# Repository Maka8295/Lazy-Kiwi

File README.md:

# Lazy-Kiwi
ESP32 based smart home device

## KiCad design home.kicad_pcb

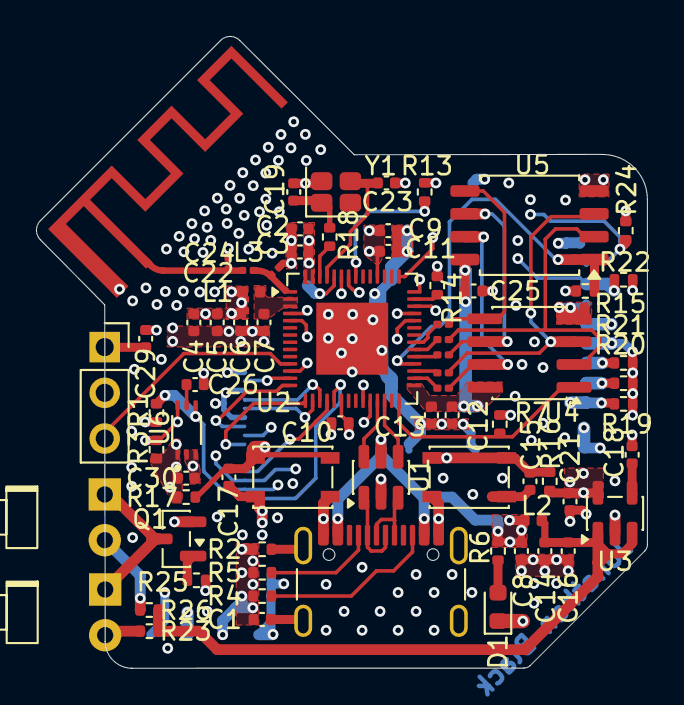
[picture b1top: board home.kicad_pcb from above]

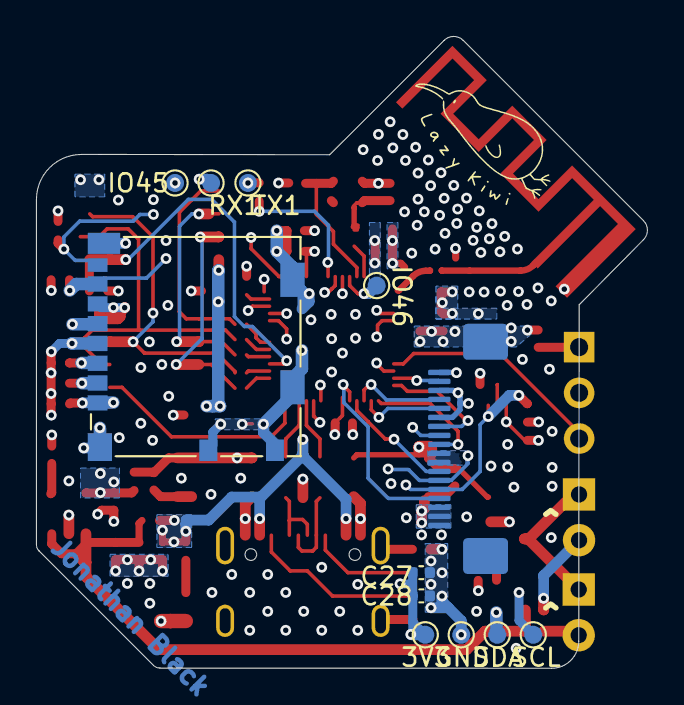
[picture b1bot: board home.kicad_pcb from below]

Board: 6 copper layers, 33.9 x 35.1 mm, 84 parts (12 on the bottom side), 60 nets.

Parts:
3V3: TestPoint; TestPoint_Pad_D1.0mm
ANT1: 50Ohm 2.4GHz PCB ANT; 2.4GHz Antenna
C1: 2.2nF; C_0402_1005Metric
C2, C5, C9, C13, C26, C27: 1uF; C_0402_1005Metric
C3: 10nF; C_0402_1005Metric
C4, C16, C21: 10uF; C_0402_1005Metric
C6, C7, C8, C10, C11, C12, C14, C15, C17, C18, C25, C28, C29, C30: 100nF; C_0402_1005Metric
C19, C23: 20pF; C_0402_1005Metric
C22, C24: 3p3F; C_0201_0603Metric
D1: LED; LED_0603_1608Metric
D3: 940nm; LED_D1.8mm_W1.8mm_H2.4mm_Horizontal_O3.81mm_Z1.6mm
GND: TestPoint; TestPoint_Pad_D1.0mm
IO45, IO46: TestPoint; TestPoint_Pad_D1.0mm
J1: USB_C_Receptacle_USB2.0_14P; USB_C_Receptacle_GCT_USB4105-xx-A_16P_TopMnt_Horizontal
J3: DISPLAY; LCSC FPC 18
J4: Micro_SD_Card; microSD_HC_Molex_104031-0811
J5: VS1838B IR Receiver; PinSocket_1x03_P2.54mm_Vertical
K^: 940nm; LED_D1.8mm_W1.8mm_H2.4mm_Horizontal_O3.81mm_Z1.6mm
L1, L2: 2n2H; L_0402_1005Metric
L3: 2n2H; L_0201_0603Metric
Q1: SS8050; SOT-23
R1, R3: 4.7kR; R_0402_1005Metric
R2: 1M; R_0402_1005Metric
R4, R5: 5.1k; R_0402_1005Metric
R6: 2.2k; R_0402_1005Metric
R7, R15, R16, R17, R19, R20, R21, R22, R24: 10k; R_0402_1005Metric
R8, R9, R10, R11, R12: 0R; R_0201_0603Metric
R13: 470R; R_0402_1005Metric
R14: 47R; R_0402_1005Metric
R18: 22R; R_0402_1005Metric
R23, R26: 47; R_0402_1005Metric
R25: 1k; R_0402_1005Metric
RX1: TestPoint; TestPoint_Pad_D1.0mm
SCL: TestPoint; TestPoint_Pad_D1.0mm
SDA: TestPoint; TestPoint_Pad_D1.0mm
SW1, SW2: SW_Push; SW_SPST_PTS810
TX1: TestPoint; TestPoint_Pad_D1.0mm
U1: USBLC6-2SC6; SOT-23-6
U2: ESP32-S3; QFN-56-1EP_7x7mm_P0.4mm_EP4x4mm
U3: SPX3819M5-L-3-3; SOT-23-5
U4: ESP-PSRAM64H; SOIC-8_3.9x4.9mm_P1.27mm
U5: W25Q128JVSIQ; SOIC-8_5.3x5.3mm_P1.27mm
U6: BH1750FVI-TR; XDCR_BH1750FVI-TR
Y1: 40MHz; Crystal_SMD_EuroQuartz_X22-4Pin_2.5x2.0mm

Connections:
3V3: 3V3.1 (1_1), C2.1, C3.1, C4.2, C5.2, C6.2, C9.2, C10.2, C11.2, C21.2, C27.2, C28.2, C29.2, C30.2, J3.1, J4.4 (VDD), J5.1, L1.2, R1.2, R3.2, R7.2, R15.2, R16.2, R17.2, R19.2, R20.2, R21.2, R22.2, R24.2, U2.20 (VDD3P3_RTC), U2.46 (VDD3P3_CPU), U2.55 (VDDA), U2.56 (VDDA), U3.5 (OUT), U6.1 (VCC)
BOOT: C17.1, R17.1, SW2.2, U2.5 (GPIO0)
CLK: J4.5 (CLK), R14.1
CMD: J4.3 (CMD), R21.1, U2.40 (GPIO35)
D+: J1.A6 (D+), J1.B6 (D+), U1.3 (I/O2), U1.4 (I/O2), U2.26 (GPIO20/USB_D+)
D-: J1.A7 (D-), J1.B7 (D-), U1.1 (I/O1), U1.6 (I/O1), U2.25 (GPIO19/USB_D-)
DAT0: J4.7 (DAT0), R22.1, U2.42 (GPIO37)
DAT1: J4.8 (DAT1), R24.1, U2.43 (GPIO38)
DAT2: J4.1 (DAT2), R19.1, U2.38 (GPIO33)
DAT3: J4.2 (DAT3/CD), R20.1, U2.39 (GPIO34)
EN: C15.1, J3.8, R16.1, SW1.2, U2.4 (CHIP_PU)
FSPICLK: J3.4, U2.17 (GPIO12)
FSPICS0: J3.9, U2.15 (GPIO10)
FSPID: J3.5, U2.16 (GPIO11)
GND: ANT1.2 (GND), C1.1, C2.2, C3.2, C4.1, C5.1, C6.1, C7.1, C8.1, C9.1, C10.1, C11.1, C12.1, C13.1, C14.1, C15.2, C16.1, C17.2, C18.1, C19.2, C21.1, C22.1, C23.1, C24.1, C25.1, C26.1, C27.1, C28.1, C29.1, C30.1, D1.1 (K), GND.1 (1_1), J1.A1 (GND), J1.A12 (GND), J1.B1 (GND), J1.B12 (GND), J3.3, J3.6, J3.10, J3.11, J3.16, J3.17, J3.18, J3.GND, J4.6 (VSS), J4.9, J4.10, J4.SH (SHIELD), J5.2, Q1.2 (E), R2.1, R4.1, R5.1, SW1.1, SW2.1, U1.2 (GND), U2.57 (GND), U3.2 (GND), U4.4 (VSS), U5.4 (GND), U6.2 (ADDR), U6.3 (GND), Y1.2 (G), Y1.4 (G)
IO45: IO45.1 (1_1), U2.51 (GPIO45)
IO46: IO46.1 (1_1), U2.52 (GPIO46)
IR-IN: J5.3, U2.11 (GPIO6)
IR-OUT: R25.1, U2.12 (GPIO7)
LCD_BL: J3.2, U2.13 (GPIO8)
LCD_DC: J3.7, U2.14 (GPIO9)
LNA_IN: C22.2, L3.1, U2.1 (LNA_IN)
unnamed: ANT1.1 (LNA), C24.2, L3.2
unnamed: C7.2, L1.1, U2.2 (VDD3P3), U2.3 (VDD3P3)
unnamed: C19.1, R18.1, Y1.1
unnamed: D1.2 (A), R6.2
unnamed: K^.2 (A), R23.2
unnamed: D3.1 (K), K^.1 (K), Q1.3 (C)
unnamed: D3.2 (A), R26.1
unnamed: J1.A5 (CC1), R5.2
unnamed: J1.B5 (CC2), R4.2
unnamed: C1.2, J1.SH (SHIELD), R2.2
unnamed: Q1.1 (B), R25.2
unnamed: C8.2, J1.A4 (VBUS), J1.A9 (VBUS), J1.B4 (VBUS), J1.B9 (VBUS), L2.1, R6.1, U1.5 (VBUS)
unnamed: R14.2, U2.41 (GPIO36)
unnamed: R10.2, U2.33 (SPICLK)
unnamed: R12.2, U2.35 (SPID)
unnamed: R8.2, U2.30 (SPIHD)
unnamed: R11.2, U2.34 (SPIQ)
unnamed: R9.2, U2.31 (SPIWP)
unnamed: R13.2, U2.49 (U0TXD)
unnamed: C18.2, U3.4 (BP)
unnamed: C26.2, U6.5 (DVI)
RX: RX1.1 (1_1), U2.50 (U0RXD)
SCL: J3.13, R3.1, SCL.1 (1_1), U2.24 (GPIO18), U6.6 (SCL)
SDA: J3.14, R1.1, SDA.1 (1_1), U2.23 (GPIO17), U6.4 (SDA)
SPICLK: R10.1, U4.6 (SCLK), U5.6 (CLK)
SPICS0: R15.1, U2.32 (SPICS0), U5.1 (~CS)
SPICS1: R7.1, U2.28 (SPICS1), U4.1 (~CE)
SPID: R12.1, U4.5 (SI/SIO), U5.5 (DI/IO_{0})
SPIHD: R8.1, U4.7 (SIO3), U5.7 (~HOLD/~RESET/IO_{3})
SPIQ: R11.1, U4.2 (SO/SIO), U5.2 (DO/IO_{1})
SPIWP: R9.1, U4.3 (SIO2), U5.3 (~WP/IO_{2})
TP_INT: J3.15, U2.19 (GPIO14)
TP_RST: J3.12, U2.18 (GPIO13)
TX: R13.1, TX1.1 (1_1)
VBUS: C14.2, C16.2, L2.2, R23.1, R26.2, U3.1 (IN), U3.3 (EN)
VCC_SPI: C12.2, C13.2, C25.2, U2.29 (VDD_SPI), U4.8 (VCC), U5.8 (VCC)
XTAL_N: C23.2, U2.53 (XTAL_N), Y1.3
XTAL_P: R18.2, U2.54 (XTAL_P)

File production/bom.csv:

Designator,Footprint,Quantity,Value,LCSC Part #
ANT1,2.4GHz Antenna,1,50Ohm 2.4GHz PCB ANT,
"C1, L1, L2",0402,3,2n2,
"C10, C11, C12, C14, C15, C17, C18, C25, C26, C30, C31, C6, C7, C8",0402,14,100n,
"C13, C2, C27, C5, C9",0402,5,1u,
"C16, C21, C4",0402,3,10u,
"C19, C23",0402,2,20p,
"C22, C24",0201,2,3p3,
C28,0402,1,1uF,
C29,0402,1,100nF,
C3,0402,1,10n,
D1,0603,1,LED,
"D2, D3",LED_D1.8mm_W1.8mm_H2.4mm_Horizontal_O3.81mm_Z1.6mm,2,940nm,
J1,USB_C_Receptacle_GCT_USB4105-xx-A_16P_TopMnt_Horizontal,1,USB_C_Receptacle_USB2.0_14P,
J2,LCSC FPC 18,1,DISPLAY,
J3,microSD_HC_Molex_104031-0811,1,Micro_SD_Card,
J4,PinSocket_1x03_P2.54mm_Vertical,1,VS1838B IR Receiver,
L3,0201,1,2n2,
Q1,SOT-23,1,SS8050,
"R1, R3, R4, R5",0402,4,5k1,
"R10, R11, R12, R8, R9",0201,5,0R,
R13,0402,1,470,
R14,0402,1,47,
"R15, R16, R17, R19, R20, R21, R22, R24, R7",0402,9,10k,
R18,0402,1,22,
R2,0402,1,1M,
"R23, R26",0805,2,47,
R25,0402,1,1k,
R6,0402,1,2k1,
"SW1, SW2",SW_SPST_PTS810,2,SW_Push,
U1,SOT-23-6,1,USBLC6-2SC6,
U2,QFN-56-1EP_7x7mm_P0.4mm_EP4x4mm,1,ESP32-S3,
U3,SOT-23-5,1,SPX3819M5-L-3-3,
U4,SOIC-8_3.9x4.9mm_P1.27mm,1,ESP-PSRAM64H,
U5,SOIC-8_5.3x5.3mm_P1.27mm,1,W25Q128JVSIQ,
U6,DFN-8-1EP_3x2mm_P0.5mm_EP1.7x1.4mm,1,MCP9808_DFN,
U7,XDCR_BH1750FVI-TR,1,BH1750FVI-TR,
Y1,Crystal_SMD_EuroQuartz_X22-4Pin_2.5x2.0mm,1,40MHz,

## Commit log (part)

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2026-06-07 Schematic
2026-06-07 kiwi
